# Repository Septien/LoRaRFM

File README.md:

The schematics for mounting a lora transciever on a board for prototyping and using the standar pin separation.

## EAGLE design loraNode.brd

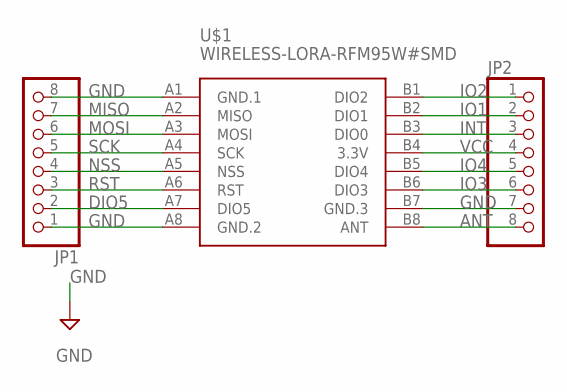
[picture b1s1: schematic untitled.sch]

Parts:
JP1, JP2: PINHD-1X8; 1X08
U$1: WIRELESS-LORA-RFM95W#SMD

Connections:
ANT: JP2.8, U$1.B8 (ANT)
DIO5: JP1.2, U$1.A7 (DIO5)
GND: JP1.1, JP1.8, JP2.7, U$1.A1 (GND.1), U$1.A8 (GND.2), U$1.B7 (GND.3)
INT: JP2.3, U$1.B3 (DIO0)
IO1: JP2.2, U$1.B2 (DIO1)
IO2: JP2.1, U$1.B1 (DIO2)
IO3: JP2.6, U$1.B6 (DIO3)
IO4: JP2.5, U$1.B5 (DIO4)
MISO: JP1.7, U$1.A2 (MISO)
MOSI: JP1.6, U$1.A3 (MOSI)
NSS: JP1.4, U$1.A5 (NSS)
RST: JP1.3, U$1.A6 (RST)
SCK: JP1.5, U$1.A4 (SCK)
VCC: JP2.4, U$1.B4 (3.3V)

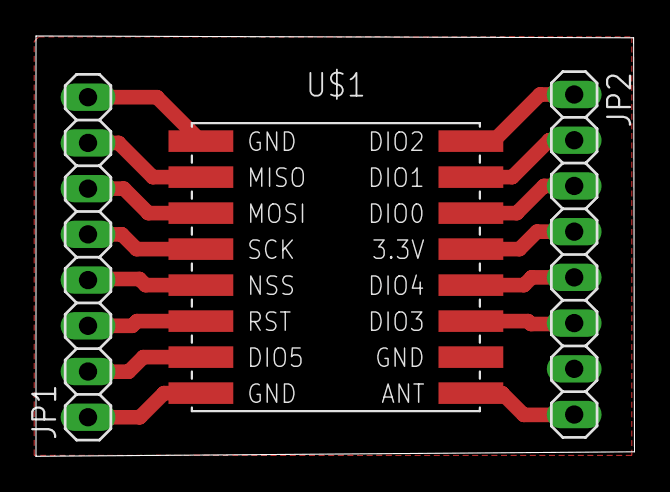
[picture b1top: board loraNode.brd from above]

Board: 2 copper layers, 33.2 x 23.4 mm, 3 parts (0 on the bottom side), 14 nets.

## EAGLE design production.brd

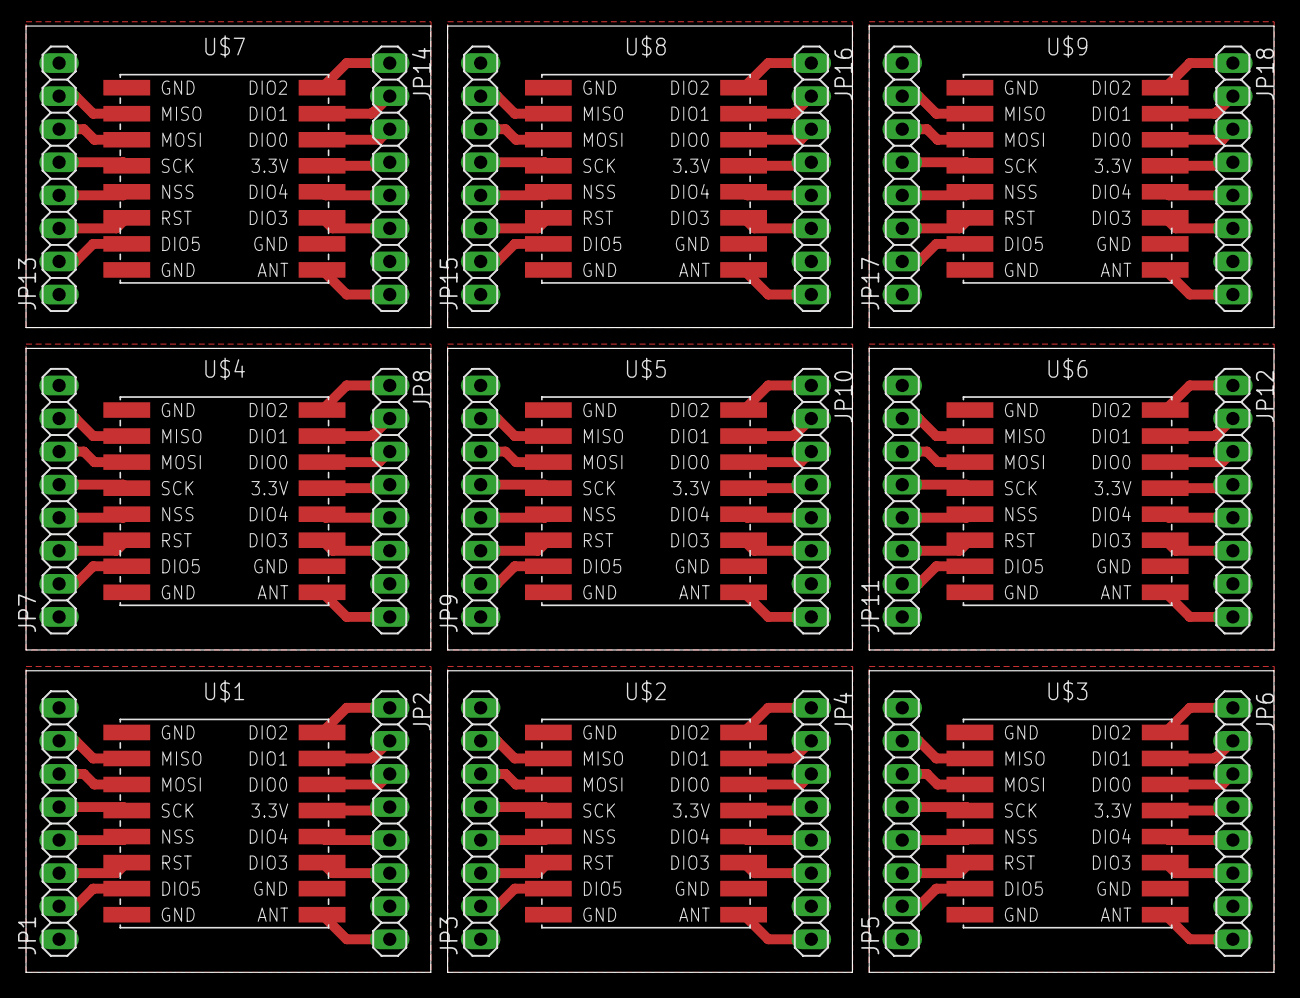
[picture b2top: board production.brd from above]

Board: 2 copper layers, 95.9 x 72.7 mm, 27 parts (0 on the bottom side), 126 nets.

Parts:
JP1, JP2, JP3, JP4, JP5, JP6, JP7, JP8, JP9, JP10, JP11, JP12, JP13, JP14, JP15, JP16, JP17, JP18: 1X08
U$1, U$2, U$3, U$4, U$5, U$6, U$7, U$8, U$9: WIRELESS-LORA-RFM95W#SMD

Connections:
ANT: JP2.8, U$1.B8
ANT1: JP4.8, U$2.B8
ANT2: JP6.8, U$3.B8
ANT3: JP8.8, U$4.B8
ANT4: JP10.8, U$5.B8
ANT5: JP12.8, U$6.B8
ANT6: JP14.8, U$7.B8
ANT7: JP16.8, U$8.B8
ANT8: JP18.8, U$9.B8
DIO1: JP3.2, U$2.A7
DIO2: JP5.2, U$3.A7
DIO3: JP7.2, U$4.A7
DIO4: JP9.2, U$5.A7
DIO5: JP1.2, U$1.A7
DIO6: JP11.2, U$6.A7
DIO7: JP13.2, U$7.A7
DIO8: JP15.2, U$8.A7
DIO9: JP17.2, U$9.A7
GND: JP1.1, JP1.8, JP2.7, U$1.A1, U$1.A8, U$1.B7
GND1: JP3.1, JP3.8, JP4.7, U$2.A1, U$2.A8, U$2.B7
GND2: JP5.1, JP5.8, JP6.7, U$3.A1, U$3.A8, U$3.B7
GND3: JP7.1, JP7.8, JP8.7, U$4.A1, U$4.A8, U$4.B7
GND4: JP9.1, JP9.8, JP10.7, U$5.A1, U$5.A8, U$5.B7
GND5: JP11.1, JP11.8, JP12.7, U$6.A1, U$6.A8, U$6.B7
GND6: JP13.1, JP13.8, JP14.7, U$7.A1, U$7.A8, U$7.B7
GND7: JP15.1, JP15.8, JP16.7, U$8.A1, U$8.A8, U$8.B7
GND8: JP17.1, JP17.8, JP18.7, U$9.A1, U$9.A8, U$9.B7
INT: JP2.3, U$1.B3
INT1: JP4.3, U$2.B3
INT2: JP6.3, U$3.B3
INT3: JP8.3, U$4.B3
INT4: JP10.3, U$5.B3
INT5: JP12.3, U$6.B3
INT6: JP14.3, U$7.B3
INT7: JP16.3, U$8.B3
INT8: JP18.3, U$9.B3
IO1: JP2.2, U$1.B2
IO2: JP2.1, U$1.B1
IO3: JP2.6, U$1.B6
IO4: JP2.5, U$1.B5
IO5: JP4.1, U$2.B1
IO6: JP4.2, U$2.B2
IO7: JP4.5, U$2.B5
IO8: JP4.6, U$2.B6
IO9: JP6.1, U$3.B1
IO10: JP6.2, U$3.B2
IO11: JP6.5, U$3.B5
IO12: JP6.6, U$3.B6
IO13: JP8.1, U$4.B1
IO14: JP8.2, U$4.B2
IO15: JP8.5, U$4.B5
IO16: JP8.6, U$4.B6
IO17: JP10.1, U$5.B1
IO18: JP10.2, U$5.B2
IO19: JP10.5, U$5.B5
IO20: JP10.6, U$5.B6
IO21: JP12.1, U$6.B1
IO22: JP12.2, U$6.B2
IO23: JP12.5, U$6.B5
IO24: JP12.6, U$6.B6
IO25: JP14.1, U$7.B1
IO26: JP14.2, U$7.B2
IO27: JP14.5, U$7.B5
IO28: JP14.6, U$7.B6
IO29: JP16.1, U$8.B1
IO30: JP16.2, U$8.B2
IO31: JP16.5, U$8.B5
IO32: JP16.6, U$8.B6
IO33: JP18.1, U$9.B1
IO34: JP18.2, U$9.B2
IO35: JP18.5, U$9.B5
IO36: JP18.6, U$9.B6
MISO: JP1.7, U$1.A2
MISO1: JP3.7, U$2.A2
MISO2: JP5.7, U$3.A2
MISO3: JP7.7, U$4.A2
MISO4: JP9.7, U$5.A2
MISO5: JP11.7, U$6.A2
MISO6: JP13.7, U$7.A2
MISO7: JP15.7, U$8.A2
MISO8: JP17.7, U$9.A2
MOSI: JP1.6, U$1.A3
MOSI1: JP3.6, U$2.A3
MOSI2: JP5.6, U$3.A3
MOSI3: JP7.6, U$4.A3
MOSI4: JP9.6, U$5.A3
MOSI5: JP11.6, U$6.A3
MOSI6: JP13.6, U$7.A3
MOSI7: JP15.6, U$8.A3
MOSI8: JP17.6, U$9.A3
NSS: JP1.4, U$1.A5
NSS1: JP3.4, U$2.A5
NSS2: JP5.4, U$3.A5
NSS3: JP7.4, U$4.A5
NSS4: JP9.4, U$5.A5
NSS5: JP11.4, U$6.A5
NSS6: JP13.4, U$7.A5
NSS7: JP15.4, U$8.A5
NSS8: JP17.4, U$9.A5
RST: JP1.3, U$1.A6
RST1: JP3.3, U$2.A6
RST2: JP5.3, U$3.A6
RST3: JP7.3, U$4.A6
RST4: JP9.3, U$5.A6
RST5: JP11.3, U$6.A6
RST6: JP13.3, U$7.A6
RST7: JP15.3, U$8.A6
RST8: JP17.3, U$9.A6
SCK: JP1.5, U$1.A4
SCK1: JP3.5, U$2.A4
SCK2: JP5.5, U$3.A4
SCK3: JP7.5, U$4.A4
SCK4: JP9.5, U$5.A4
SCK5: JP11.5, U$6.A4
SCK6: JP13.5, U$7.A4
SCK7: JP15.5, U$8.A4
SCK8: JP17.5, U$9.A4
VCC: JP2.4, U$1.B4
VCC1: JP4.4, U$2.B4
VCC2: JP6.4, U$3.B4
VCC3: JP8.4, U$4.B4
VCC4: JP10.4, U$5.B4
VCC5: JP12.4, U$6.B4
VCC6: JP14.4, U$7.B4
VCC7: JP16.4, U$8.B4
VCC8: JP18.4, U$9.B4

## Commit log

2020-05-11 First commit.
2020-05-13 Add production board.
2020-05-13 Remove untitled file.
2020-05-13 Add lora node board and schematics.
2020-05-13 Add .gitignore.

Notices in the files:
parts and their libraries:
dht22: Released under the Creative Commons Attribution 4.0 International License: http://creativecommons.org/licenses/by/4.0
